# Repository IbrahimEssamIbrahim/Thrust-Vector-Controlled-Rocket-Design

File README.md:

# <a href="https://a360.co/3PXAbBp"> Thrust-Vector-Controlled-Rocket-Design </a>

This project proposes the development of a Thrust Vector-Controlled (TVC) rocket as an alternative to drones for high-altitude payload delivery. Drones face limitations such as
cost, payload size restrictions, and reliance on air density, making them inefficient for high-altitude missions. The TVC rocket, inspired by SpaceX's Falcon Heavy, utilizes 
thrust vector control for precise navigation and payload delivery regardless of air density.

The project aims for cost-effectiveness by using off-the-shelf components like pressure sensors, IMUs, and Arduinos, integrated into a single PCB. This approach, coupled with
lightweight 3D-printed materials for the rocket chassis, aims to reduce costs significantly.

Applications include academic research and medical deliveries to remote areas. The rocket's design focuses on stability optimization, utilizing OpenRocket software for
simulations and Fusion 360 for 3D component design. Additionally, a water pressure chamber was introduced for cost-effective testing.

The flight computer comprises various sensors for monitoring acceleration, rotation, and altitude, essential for making critical flight decisions. These include MPU6050 IMUs, 
BMP280 barometers, EEPROMs, and battery level monitors.

Overall, the TVC rocket project offers an affordable and efficient solution for high-altitude payload delivery, potentially revolutionizing academic and humanitarian applications.

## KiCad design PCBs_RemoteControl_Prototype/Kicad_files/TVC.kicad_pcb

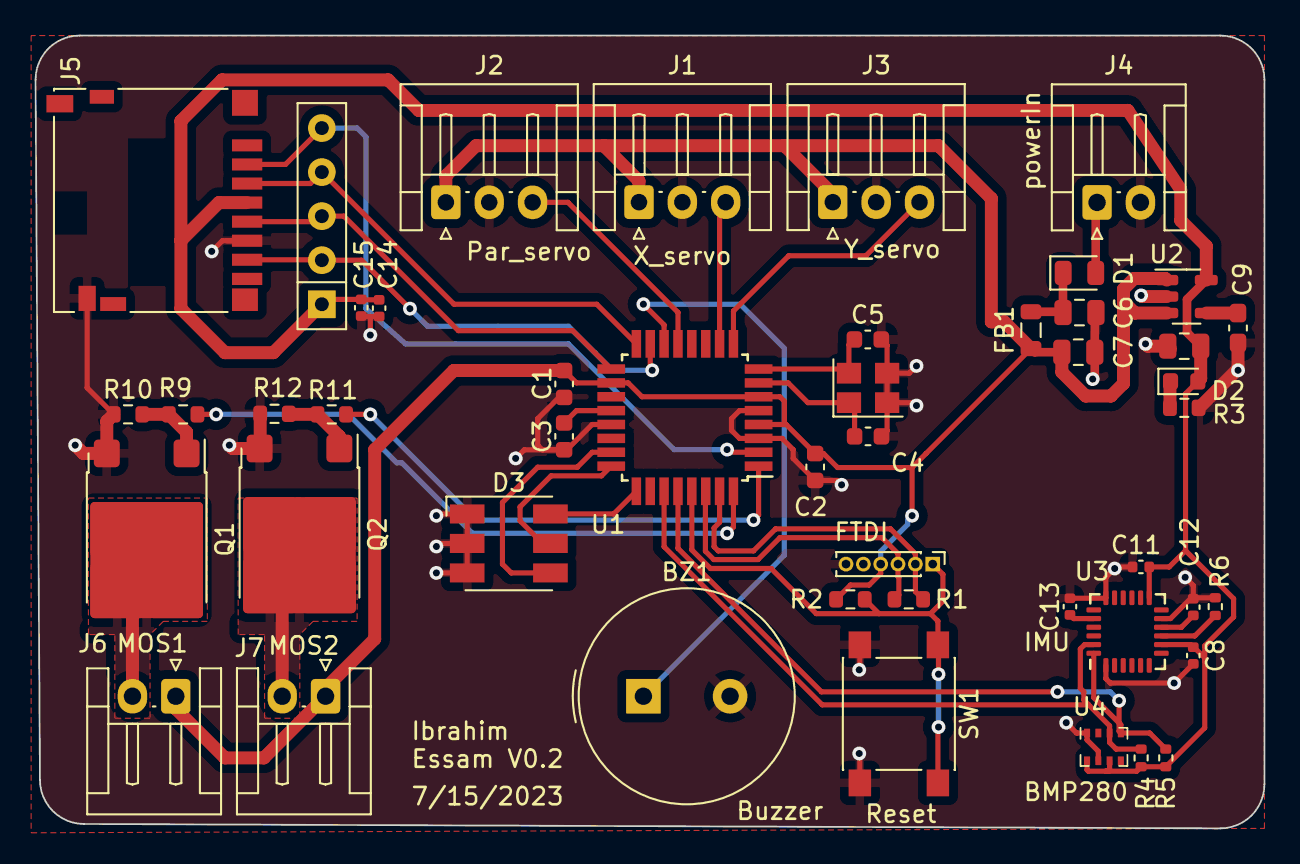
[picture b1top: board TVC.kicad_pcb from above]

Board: 2 copper layers, 70.9 x 45.7 mm, 47 parts (0 on the bottom side), 35 nets.

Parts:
BZ1: Buzzer; Buzzer_TDK_PS1240P02BT_D12.2mm_H6.5mm
C1, C2, C3: 100n; C_0603_1608Metric
C4, C5: 22p; C_0603_1608Metric
C6, C7, C10: 2u2; C_0805_2012Metric
C8: 10n; C_0402_1005Metric
C9: 100n; C_0603_1608Metric_Pad1.08x0.95mm_HandSolder
C11, C12, C14: 100n; C_0402_1005Metric
C13: 2n2; C_0402_1005Metric
C15: 10u; C_0402_1005Metric
D1: D; D_0805_2012Metric
D2: RED; LED_0603_1608Metric
D3: LED_RGB; LED_RGB_5050-6
FB1: FerriteBead; L_0805_2012Metric
J1: X_servo; JST_EH_S3B-EH_1x03_P2.50mm_Horizontal
J2: Par_servo; JST_EH_S3B-EH_1x03_P2.50mm_Horizontal
J3: Y_servo; JST_EH_S3B-EH_1x03_P2.50mm_Horizontal
J4: powerIn; JST_EH_S2B-EH_1x02_P2.50mm_Horizontal
J5: Micro_SD_Card; microSD_HC_Hirose_DM3D-SF
J6: MOS1; JST_EH_S2B-EH_1x02_P2.50mm_Horizontal
J7: MOS2; JST_EH_S2B-EH_1x02_P2.50mm_Horizontal
J8: FTDI; PinHeader_1x06_P1.00mm_Vertical
Q1, Q2: IRF540N; ATPAK-2
R1, R2: 1K; R_0603_1608Metric
R3: 470R; R_0603_1608Metric
R4, R5, R6: 4k7; R_0402_1005Metric
R9, R11: 100; R_0603_1608Metric
R10, R12: 10K; R_0603_1608Metric
RN1: R_Network04; R_Array_SIP5
SW1: SW_Push; SW_SPST_PTS645
U1: ATmega328PB-A; TQFP-32_7x7mm_P0.8mm
U2: SPX3819M5-L; SOT-23-5
U3: MPU-6050; InvenSense_QFN-24_4x4mm_P0.5mm
U4: BMP280; Bosch_LGA-8_2x2.5mm_P0.65mm_ClockwisePinNumbering
Y1: 16MHz; Crystal_SMD_3225-4Pin_3.2x2.5mm

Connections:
+3.3V: C8.1, C10.1, C11.1, C14.1, C15.1, D2.2 (A), J5.4 (VDD), R4.1, R5.1, RN1.1 (common), U2.5 (OUT), U3.8 (VLOGIC), U3.13 (VDD), U4.6 (VDDIO), U4.8 (VDD)
+5V: C1.1, C2.1, C7.1, FB1.2, J1.1, J2.1, J3.1, J6.1, J7.1, J8.4, R2.1, U1.4 (VCC), U1.6 (PE1), U1.18 (AVCC), U2.1 (IN), U2.3 (EN)
/AREF: C3.1, U1.20 (AREF)
/Buzzer: BZ1.1 (-), U1.14 (PB2)
/CS: J5.2 (DAT3/CD), RN1.5 (R4), U1.2 (PD4)
/LED_B: D3.6 (RA), U1.25 (PC2)
/LED_G: D3.5 (GA), U1.24 (PC1)
/LED_R: D3.4 (BA), U1.23 (PC0)
/M1_in: R9.1, U1.32 (PD2)
/M1_out: J6.2, Q1.2 (D)
/M2_in: R11.1, U1.1 (PD3)
/M2_out: J7.2, Q2.2 (D)
/MISO: J5.3 (CMD), RN1.4 (R3), U1.16 (PB4)
/MOSI: J5.7 (DAT0), RN1.2 (R1), U1.15 (PB3)
/Par_servo: J2.3, U1.13 (PB1)
/RST: J8.1, R2.2, SW1.1, U1.29 (~RESET/PC6)
/RX: J8.3, R1.1, U1.30 (PD0)
/SCK: J5.5 (CLK), RN1.3 (R2), U1.17 (PB5)
/TX: J8.2, R1.2, U1.31 (PD1)
/XTAL1: C4.1, U1.7 (XTAL1/PB6), Y1.1
/XTAL2: C5.1, U1.8 (XTAL2/PB7), Y1.4
/X_servo: J1.3, U1.10 (PD6)
/Y_servo: J3.3, U1.9 (PD5)
AD0: R6.2, U3.9 (AD0)
GND: BZ1.2 (+), C1.2, C2.2, C3.2, C4.2, C5.2, C6.2, C7.2, C8.2, C9.2, C10.2, C11.2, C12.2, C13.2, C14.2, C15.2, D3.1 (RK), D3.2 (GK), D3.3 (BK), J1.2, J2.2, J3.2, J4.2, J5.6 (VSS), J5.9 (SHIELD), J8.6, Q1.3 (S), Q2.3 (S), R3.2, R6.1, R10.1, R12.1, SW1.2, U1.3 (PE0), U1.5 (GND), U1.21 (GND), U2.2 (GND), U3.1 (CLKIN), U3.11 (FSYNC), U3.18 (GND), U4.1 (GND), U4.7 (GND), Y1.2, Y1.3
unnamed: D1.2 (A), J4.1
unnamed: C6.1, D1.1 (K), FB1.1
unnamed: D2.1 (K), R3.1
unnamed: Q1.1 (G), R9.2, R10.2
unnamed: Q2.1 (G), R11.2, R12.2
unnamed: C9.1, U2.4 (ADJ)
unnamed: C13.1, U3.20 (CPOUT)
unnamed: C12.1, U3.10 (REGOUT)
SCL: R4.2, U1.27 (PC4), U3.23 (SCL), U4.3 (SDI)
SDA: R5.2, U1.28 (PC5), U3.24 (SDA), U4.4 (SCK)
